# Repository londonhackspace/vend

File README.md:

Kicad files for motor driver board

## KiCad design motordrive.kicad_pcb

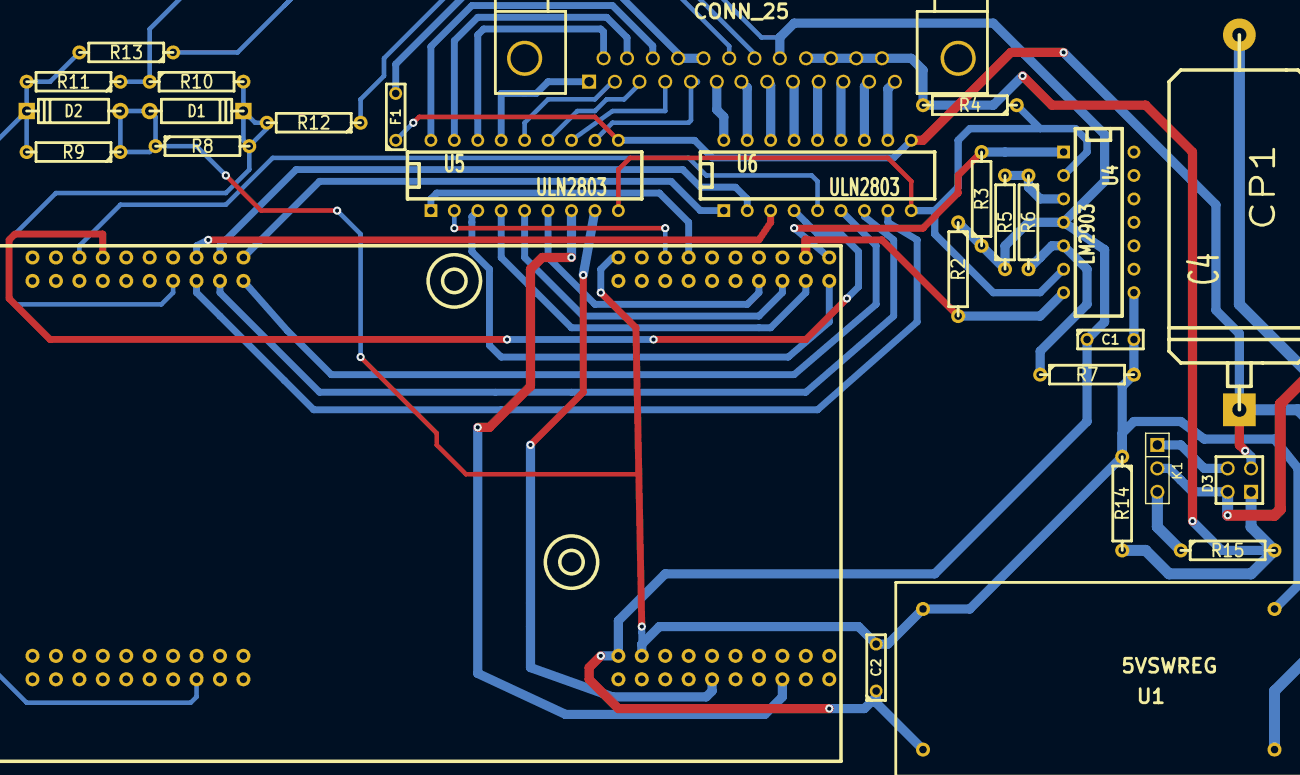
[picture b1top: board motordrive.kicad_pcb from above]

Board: 2 copper layers, 28 parts (0 on the bottom side), 49 nets.

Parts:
C1, C2: C; C2
C4: CP1; CP16
D1, D2: 3v3; D4
D3: BRIDGE; PIN_ARRAY_2X2
F1: FUSE; C2
J1: TI_CONN_LAUNCHPAD; Conn_Launch_Pad
K1: CONN_3; PIN_ARRAY_3X1
P2: CONN_25; DB25FC
R2, R3: 4k7; R4
R4: 1R5; R4
R5, R6, R7: R; R4
R8, R9, R10, R11: 8k2; R4
R12, R13: 2k2; R4
R14, R15: 0R; R4
U1: 5VSWREG; SWREG-X4
U4: LM2903; DIP-14__300
U5, U6: ULN2803; DIP-18__300

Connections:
+5V: C1.1, C2.1, J1.11, P2.21, R2.1, R3.1, R5.1, R10.1, R11.1, U1.3, U4.4
+24V: C4.1, D3.3, F1.1, U1.4, U5.10, U6.10
/30mV: R6.2, R7.1, U4.5
/640mV: R5.2, R6.1, U4.3
GND: C1.2, C2.2, D1.1, D2.1, J1.12, J1.31, R7.2, R8.1, R9.1, R14.1, U1.1, U1.2, U4.8
GNDA: D3.1, P2.22, P2.23, P2.24, P2.25, R4.2, R14.2, R15.2
unnamed: R4.1, U4.2, U4.6, U5.9, U6.9
unnamed: P2.19, R12.1
unnamed: P2.20, R13.1
unnamed: K1.3, R15.1
unnamed: P2.12, U6.12
unnamed: P2.2, U5.14
unnamed: P2.14, U5.16
unnamed: P2.16, U5.18
unnamed: P2.7, U6.17
unnamed: P2.9, U6.15
unnamed: P2.13, U6.11
unnamed: P2.15, U5.17
unnamed: P2.1, U5.15
unnamed: P2.3, U5.13
unnamed: P2.5, U5.11
unnamed: F1.2, P2.17, P2.18
unnamed: D3.4, K1.1
unnamed: J1.33, U5.2
unnamed: J1.70, U6.6
unnamed: J1.73, U6.5
unnamed: J1.74, U6.4
unnamed: J1.78, U6.3
unnamed: J1.79, U6.2
unnamed: J1.80, U6.1
unnamed: J1.34, U5.1
unnamed: J1.30, U5.3
unnamed: J1.29, U5.4
unnamed: J1.28, U5.5
unnamed: J1.39, R2.2, U4.7
unnamed: J1.40, R3.2, U4.1
unnamed: J1.27, U5.6
unnamed: J1.68, U6.8
unnamed: J1.69, U6.7
unnamed: P2.8, U6.16
unnamed: P2.6, U6.18
unnamed: P2.4, U5.12
unnamed: D2.2, J1.48, R9.2, R11.2, R13.2
unnamed: C4.2, D3.2, K1.2
unnamed: D1.2, J1.67, R8.2, R10.2, R12.2
unnamed: J1.8, U5.7
unnamed: J1.5, U5.8
unnamed: P2.11, U6.13
unnamed: P2.10, U6.14

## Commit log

2014-10-08 Deleted rPi connector in sch, partially in brd
2014-10-08 Tidied .brd and saved, no other changes
2014-11-16 added launcpad footprint in new launchpad
2014-12-27 Modded motordrive.pro + lib/Launchpad.mod I think
2014-12-27 added pdf
2014-12-27 Added boosterpack lib + components + module
2014-12-28 Arduino + shifters gone, Launchpad in, PCB mess
2014-12-28 Actually commit all - new ratsnest too
2014-12-28 Deleted unwanted crap
2014-12-28 Some routing
2014-12-28 Finished Initial routing og PCB
2014-12-29 Tidying
2015-04-28 new updates
2015-04-28 test add
2015-04-28 decent track widths
2015-04-28 bit of shuffling
2015-08-25 Added gerber zip
